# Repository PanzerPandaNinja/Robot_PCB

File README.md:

# Robot_PCB
First try with generic robot PCB

Requires: 
https://github.com/jenschr/ESP32-workshop-files/tree/main/ESP32_S2_MINI_1
https://github.com/jenschr/USB-C-Connectors

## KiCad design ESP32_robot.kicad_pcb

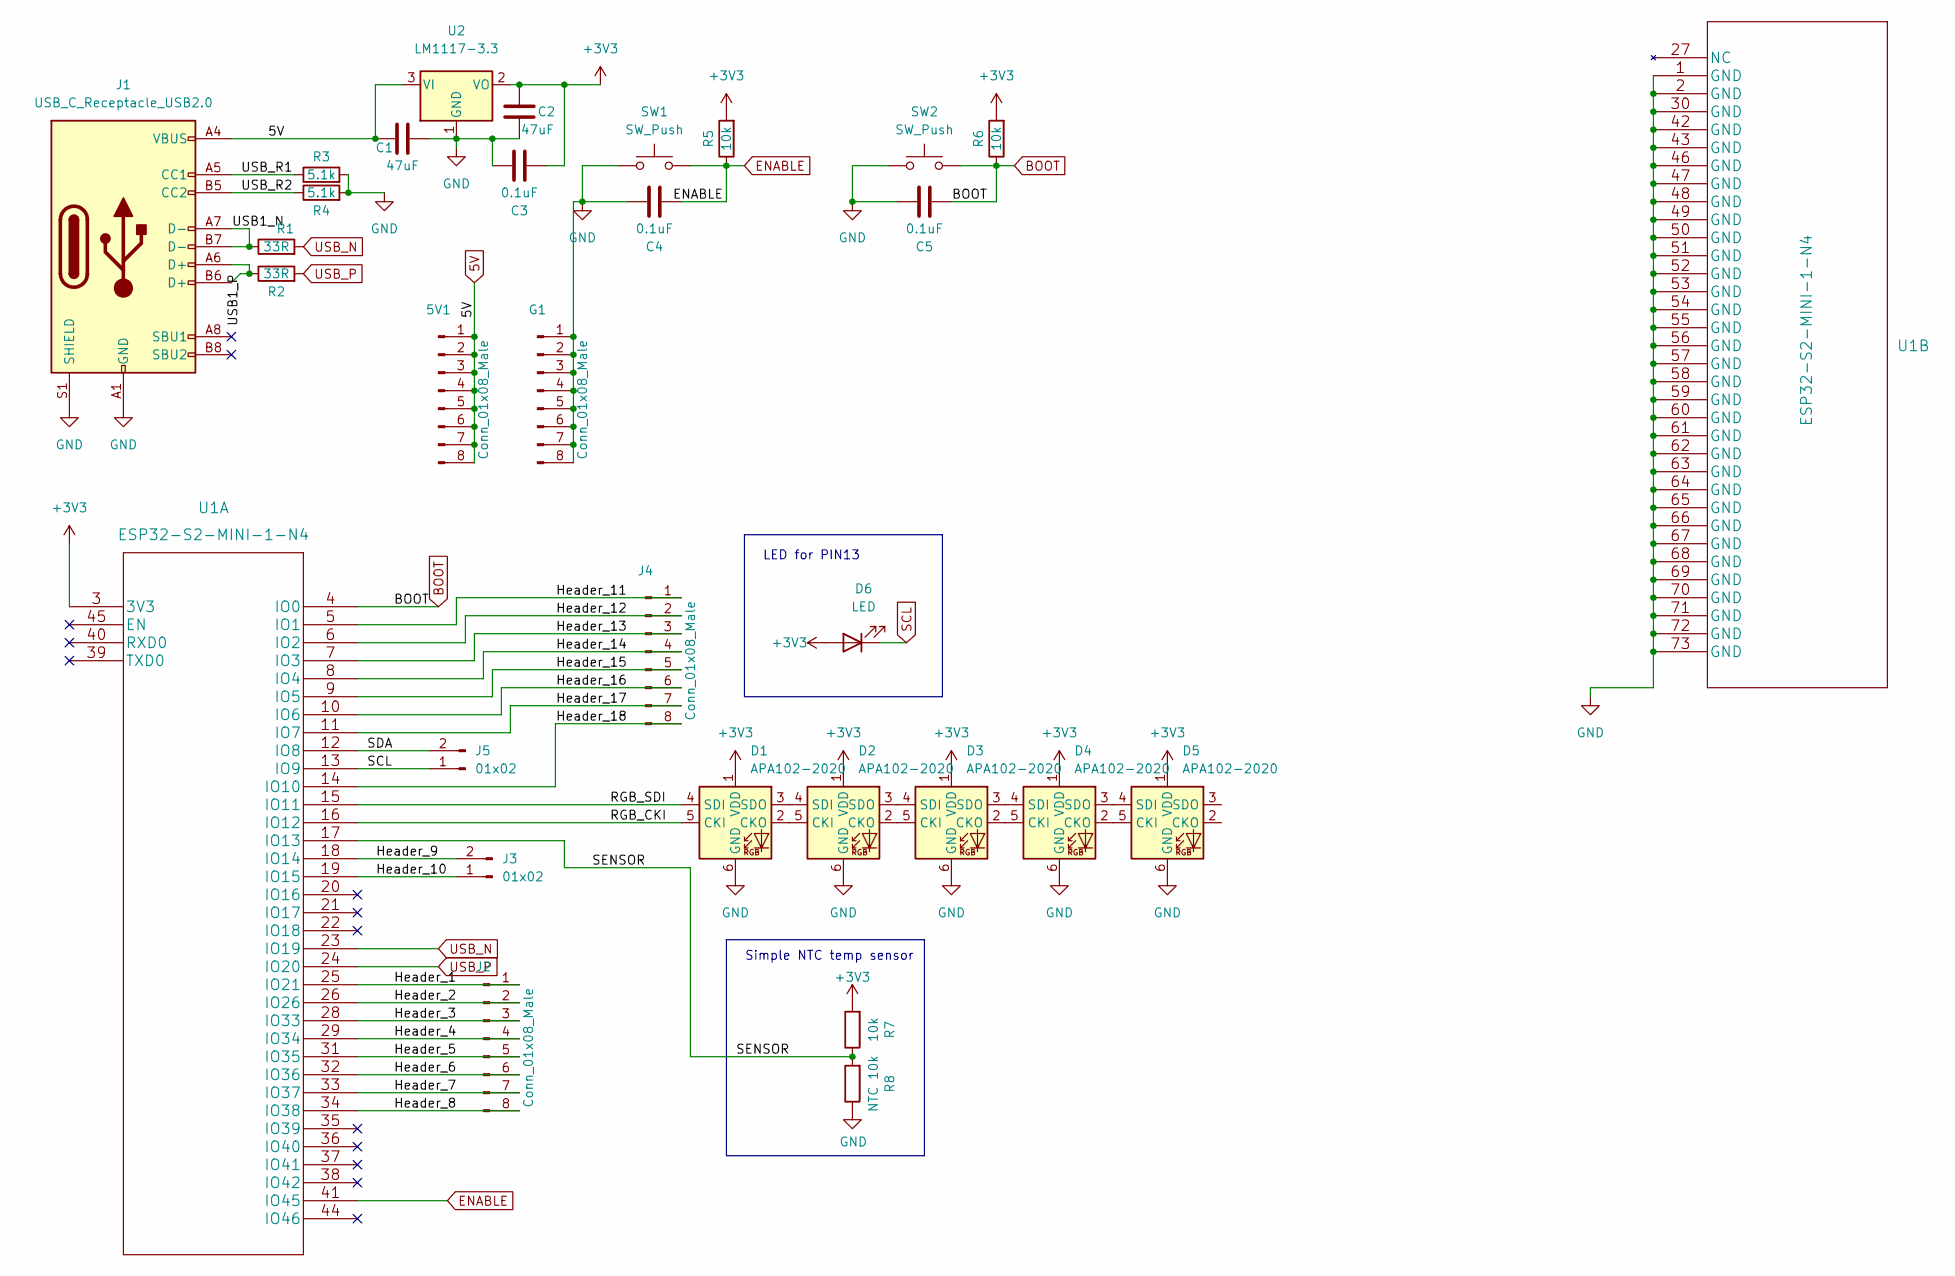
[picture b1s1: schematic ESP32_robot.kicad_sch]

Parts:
5V1: Conn_01x08_Male; PinHeader_1x08_P2.54mm_Vertical
C1, C2: 47uF; C_0805_2012Metric
C3, C4, C5: 0.1uF; C_0603_1608Metric
D1, D2, D3, D4, D5: APA102-2020; LED-APA102-2020
D6: LED; LED_0603_1608Metric
G1: Conn_01x08_Male; PinHeader_1x08_P2.54mm_Vertical
J1: USB_C_Receptacle_USB2.0; TYPE-C-31-M-12
J2, J4: Conn_01x08_Male; PinHeader_1x08_P2.54mm_Vertical
J3, J5: 01x02; PinHeader_1x02_P2.54mm_Vertical
R1, R2: 33R; R_0603_1608Metric_Pad0.98x0.95mm_HandSolder
R3, R4: 5.1k; R_0603_1608Metric_Pad0.98x0.95mm_HandSolder
R5, R6: 10k; R_0603_1608Metric_Pad0.98x0.95mm_HandSolder
R7: 10k; R_0402_1005Metric; MPN RMCF0603JG10K0
R8: NTC 10k; R_0402_1005Metric; MPN RMCF0603JG10K0
SW1, SW2: SW_Push; SW_SPST_Panasonic_EVQPL_3PL_5PL_PT_A08
U1: ESP32-S2-MINI-1-N4
U2: LM1117-3.3; SOT-223

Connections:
5V: 5V1.1, 5V1.2, 5V1.3, 5V1.4, 5V1.5, 5V1.6, 5V1.7, 5V1.8, C1.2, J1.A4 (VBUS), J1.A9 (VBUS), J1.B4 (VBUS), J1.B9 (VBUS), U2.3 (VI)
+3V3: C2.2, C3.2, D1.1 (VDD), D2.1 (VDD), D3.1 (VDD), D4.1 (VDD), D5.1 (VDD), D6.2 (A), R5.2, R6.2, R7.2, U1.3 (3V3), U2.2 (VO)
/Header_1: J2.1, U1.25 (IO21)
/Header_2: J2.2, U1.26 (IO26)
/Header_3: J2.3, U1.28 (IO33)
/Header_4: J2.4, U1.29 (IO34)
/Header_5: J2.5, U1.31 (IO35)
/Header_6: J2.6, U1.32 (IO36)
/Header_7: J2.7, U1.33 (IO37)
/Header_8: J2.8, U1.34 (IO38)
/Header_9: J3.2, U1.18 (IO14)
/Header_10: J3.1, U1.19 (IO15)
/Header_11: J4.1, U1.5 (IO1)
/Header_12: J4.2, U1.6 (IO2)
/Header_13: J4.3, U1.7 (IO3)
/Header_14: J4.4, U1.8 (IO4)
/Header_15: J4.5, U1.9 (IO5)
/Header_16: J4.6, U1.10 (IO6)
/Header_17: J4.7, U1.11 (IO7)
/Header_18: J4.8, U1.14 (IO10)
/RGB_CKI: D1.5 (CKI), U1.16 (IO12)
/RGB_SDI: D1.4 (SDI), U1.15 (IO11)
/SDA: J5.2, U1.12 (IO8)
/SENSOR: R7.1, R8.2, U1.17 (IO13)
/USB1_N: J1.A7 (D-), J1.B7 (D-), R1.1
/USB1_P: J1.A6 (D+), J1.B6 (D+), R2.1
/USB_R1: J1.A5 (CC1), R3.1
/USB_R2: J1.B5 (CC2), R4.1
BOOT: C5.2, R6.1, SW2.2, U1.4 (IO0)
ENABLE: C4.2, R5.1, SW1.2, U1.41 (IO45)
GND: C1.1, C2.1, C3.1, C4.1, C5.1, D1.6 (GND), D2.6 (GND), D3.6 (GND), D4.6 (GND), D5.6 (GND), G1.1, G1.2, G1.3, G1.4, G1.5, G1.6, G1.7, G1.8, J1.A1 (GND), J1.A12 (GND), J1.B1 (GND), J1.B12 (GND), J1.S1 (SHIELD), R3.2, R4.2, R8.1, SW1.1, SW2.1, U1.1 (GND), U1.2 (GND), U1.30 (GND), U1.42 (GND), U1.43 (GND), U1.46 (GND), U1.47 (GND), U1.48 (GND), U1.49 (GND), U1.50 (GND), U1.51 (GND), U1.52 (GND), U1.53 (GND), U1.54 (GND), U1.55 (GND), U1.56 (GND), U1.57 (GND), U1.58 (GND), U1.59 (GND), U1.60 (GND), U1.61 (GND), U1.62 (GND), U1.63 (GND), U1.64 (GND), U1.65 (GND), U1.66 (GND), U1.67 (GND), U1.68 (GND), U1.69 (GND), U1.70 (GND), U1.71 (GND), U1.72 (GND), U1.73 (GND), U2.1 (GND)
unnamed: D1.2 (CKO), D2.5 (CKI)
unnamed: D1.3 (SDO), D2.4 (SDI)
unnamed: D2.2 (CKO), D3.5 (CKI)
unnamed: D2.3 (SDO), D3.4 (SDI)
unnamed: D3.2 (CKO), D4.5 (CKI)
unnamed: D3.3 (SDO), D4.4 (SDI)
unnamed: D4.2 (CKO), D5.5 (CKI)
unnamed: D4.3 (SDO), D5.4 (SDI)
SCL: D6.1 (K), J5.1, U1.13 (IO9)
USB_N: R1.2, U1.23 (IO19)
USB_P: R2.2, U1.24 (IO20)

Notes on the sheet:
Simple NTC temp sensor
LED for PIN13

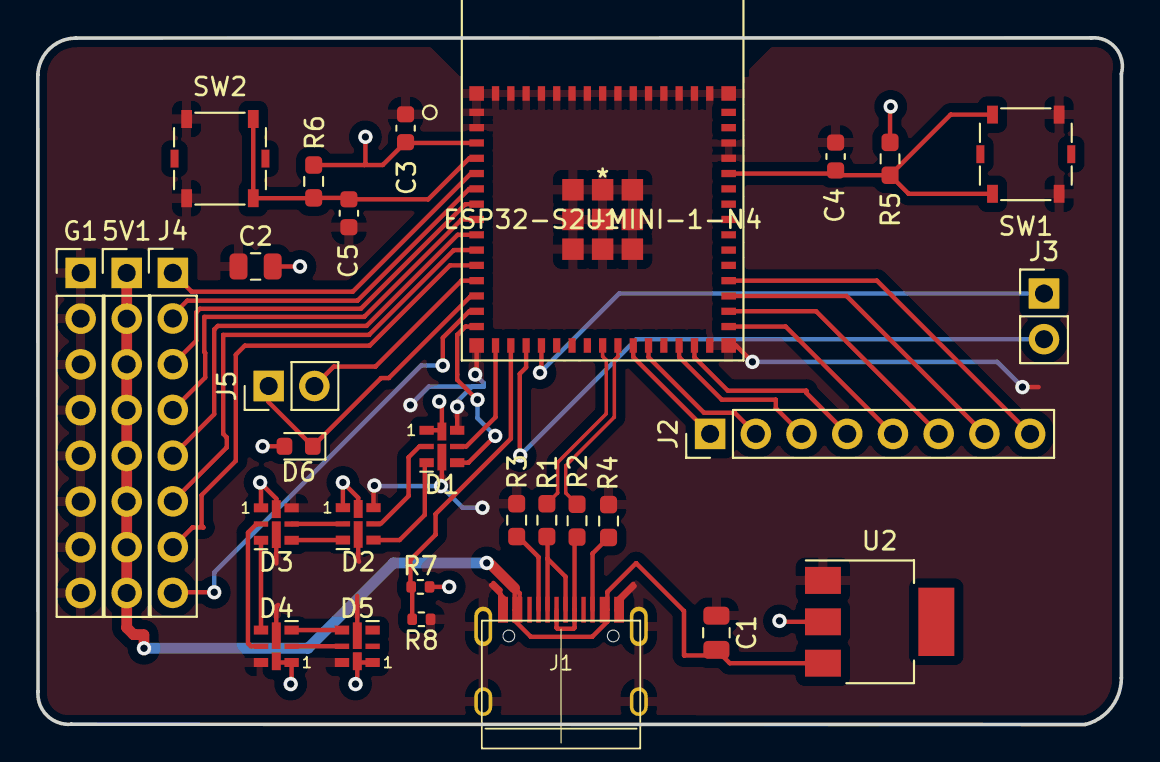
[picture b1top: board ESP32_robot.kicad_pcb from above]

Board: 2 copper layers, 60.3 x 38.2 mm, 30 parts (0 on the bottom side), 42 nets.

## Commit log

2022-04-07 First version without significant errors
2024-02-29 hopefully the latest

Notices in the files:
parts and their libraries:
Copyright 2021 Accelerated Designs. All rights reserved.
